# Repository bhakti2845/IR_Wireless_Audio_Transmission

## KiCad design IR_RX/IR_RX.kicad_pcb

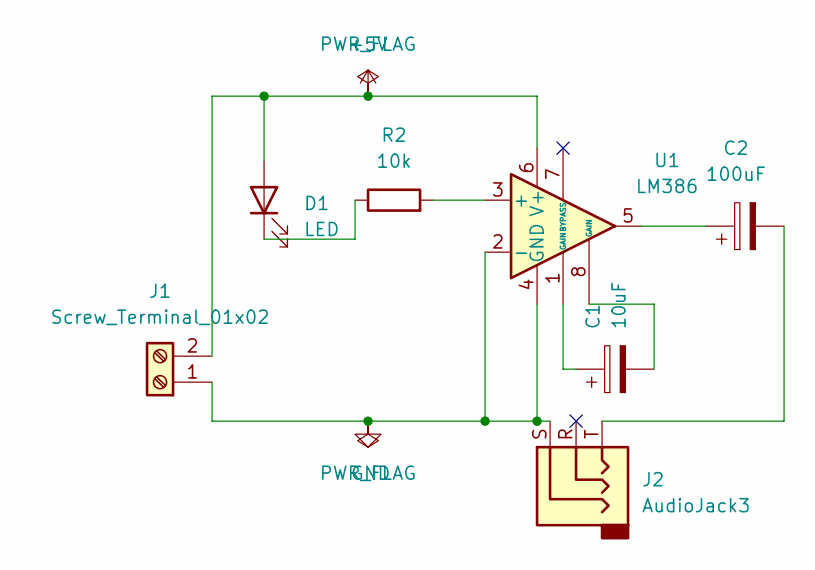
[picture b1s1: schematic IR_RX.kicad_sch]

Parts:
C1: 10uF; CP_Radial_D5.0mm_P2.50mm
C2: 100uF; CP_Radial_D8.0mm_P2.50mm
D1: LED; LED_D5.0mm_IRBlack
J1: Screw_Terminal_01x02; Altech_AK100_1x02_P5.00mm
J2: AudioJack3; Jack_3.5mm_CUI_SJ1-3533NG_Horizontal_CircularHoles
R2: 10k; R_Axial_DIN0207_L6.3mm_D2.5mm_P7.62mm_Horizontal
U1: LM386; DIP-8_W7.62mm_LongPads

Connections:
+5V: D1.2 (A), J1.2, U1.6 (V+)
GND: J1.1, J2.S, U1.2 (-), U1.4 (GND)
unnamed: C1.1, U1.1 (GAIN)
unnamed: C1.2, U1.8 (GAIN)
unnamed: C2.1, U1.5
unnamed: C2.2, J2.T
unnamed: D1.1 (K), R2.1
unnamed: R2.2, U1.3 (+)

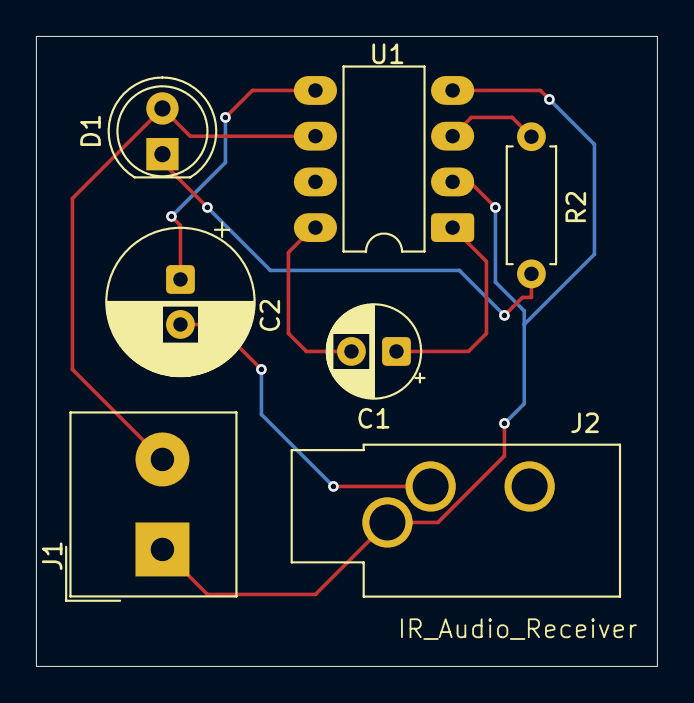
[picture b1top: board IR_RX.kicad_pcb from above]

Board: 2 copper layers, 34.5 x 35.0 mm, 7 parts (0 on the bottom side), 8 nets.

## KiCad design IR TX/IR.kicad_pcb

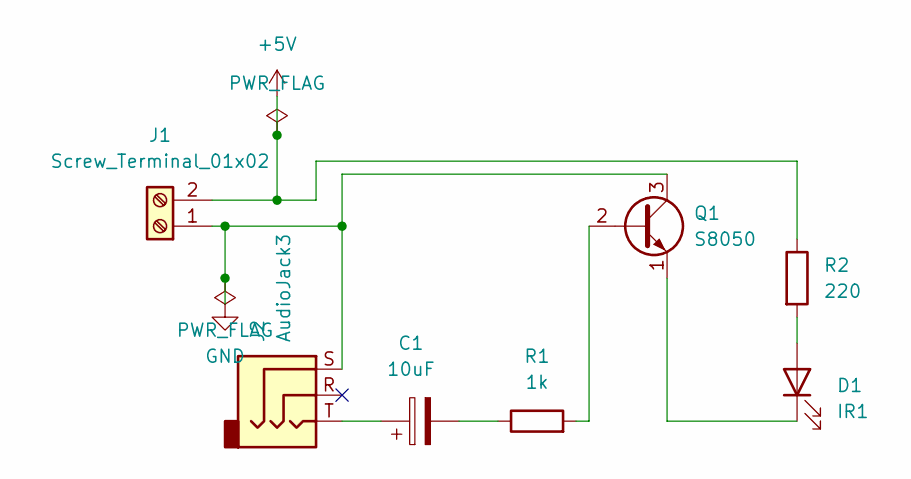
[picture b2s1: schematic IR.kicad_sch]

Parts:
C1: 10uF; CP_Radial_D5.0mm_P2.00mm
D1: IR1; LED_D5.0mm_IRGrey
J1: Screw_Terminal_01x02; TerminalBlock_Altech_AK300-2_P5.00mm
J2: AudioJack3; Jack_3.5mm_CUI_SJ1-3533NG_Horizontal_CircularHoles
Q1: S8050; TO-92_Inline
R1: 1k; R_Axial_DIN0207_L6.3mm_D2.5mm_P7.62mm_Horizontal
R2: 220; R_Axial_DIN0207_L6.3mm_D2.5mm_P7.62mm_Horizontal

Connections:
+5V: J1.2, R2.1
GND: J1.1, J2.S, Q1.3 (C)
unnamed: C1.1, J2.T
unnamed: C1.2, R1.1
unnamed: D1.2 (A), R2.2
unnamed: D1.1 (K), Q1.1 (E)
unnamed: Q1.2 (B), R1.2

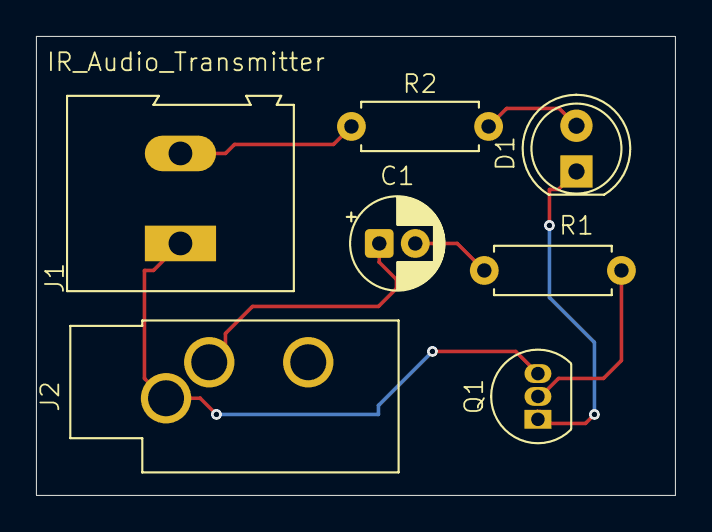
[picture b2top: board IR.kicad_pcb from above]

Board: 2 copper layers, 35.5 x 25.5 mm, 7 parts (0 on the bottom side), 7 nets.

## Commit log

2025-08-16 Initial commit of PCB project files
